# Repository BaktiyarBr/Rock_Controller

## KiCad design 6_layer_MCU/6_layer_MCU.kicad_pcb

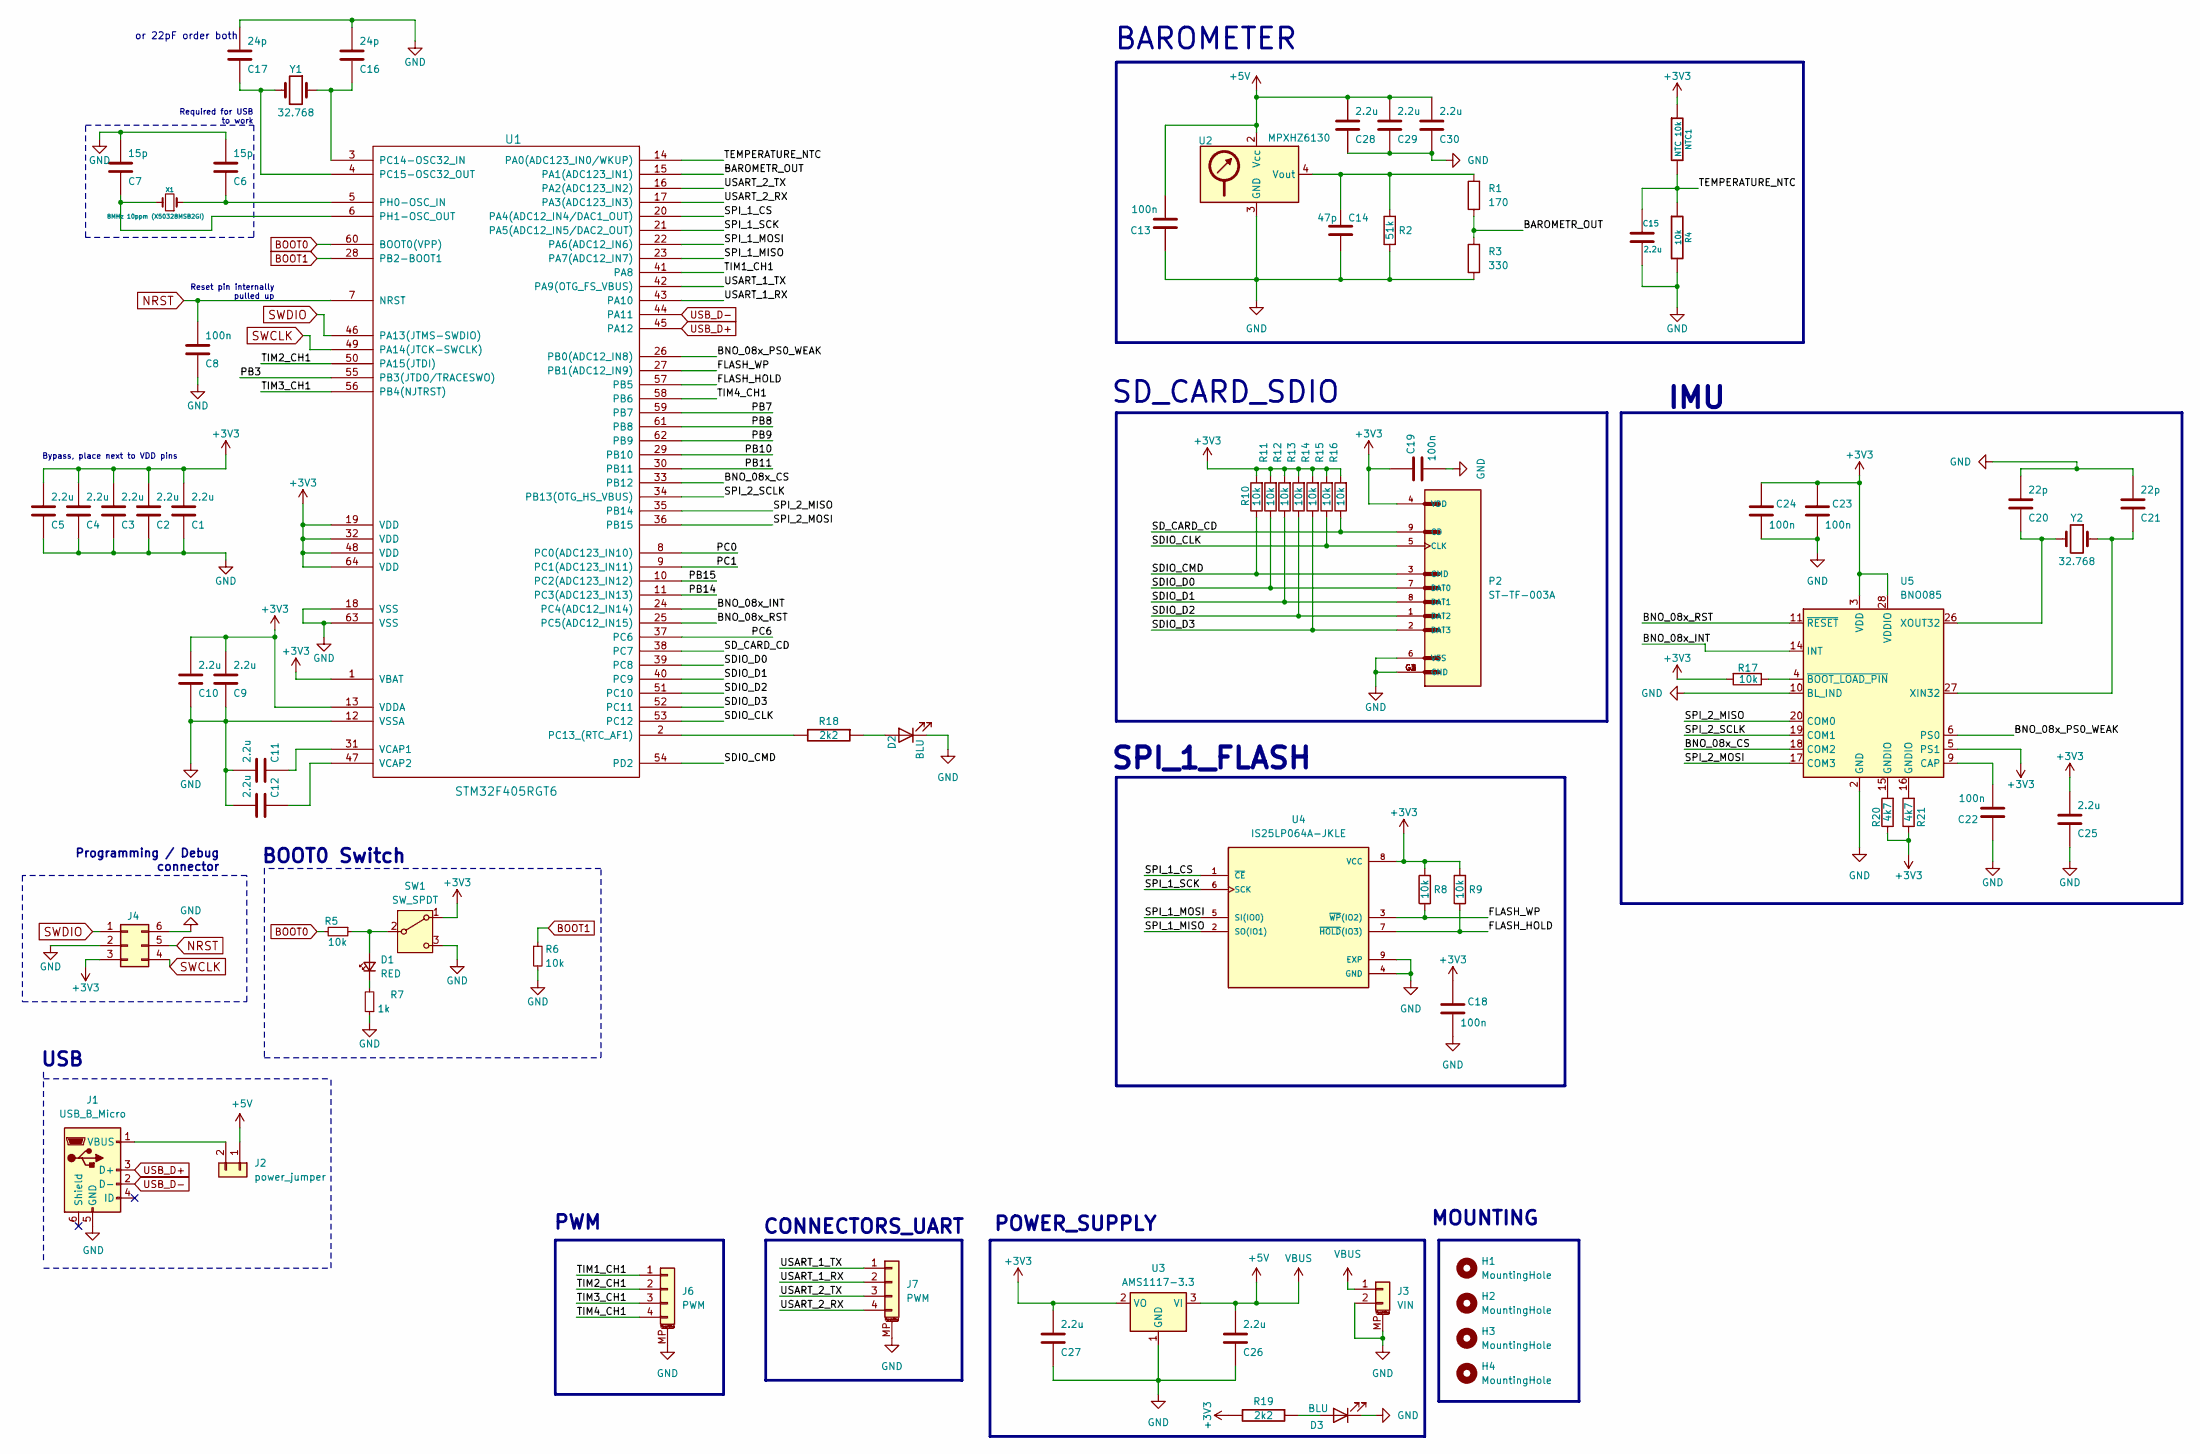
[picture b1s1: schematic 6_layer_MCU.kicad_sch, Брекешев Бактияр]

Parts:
C1, C2, C3, C4, C5, C9, C10, C11, C12, C15, C25, C26, C27, C28, C29, C30: 2.2u; C_0603_1608Metric
C6, C7: 15p; C_0603_1608Metric
C8, C13, C18, C19, C22, C23, C24: 100n; C_0603_1608Metric
C14: 47p; C_0603_1608Metric_Pad1.08x0.95mm_HandSolder
C16, C17: 24p; C_0603_1608Metric
C20, C21: 22p; C_0603_1608Metric
D1: RED; LED_0603_1608Metric; LCSC Part # C2286
D2, D3: BLU; LED_0603_1608Metric
H1, H2, H3, H4: MountingHole; MountingHole_2.2mm_M2
J1: USB_B_Micro; USB_Mini-B_Lumberg_2486_01_Horizontal
J2: power_jumper; PinHeader_1x02_P1.00mm_Vertical
J3: VIN; JST_GH_SM02B-GHS-TB_1x02-1MP_P1.25mm_Horizontal
J4: Conn_02x03_Counter_Clockwise; PinHeader_2x03_P2.54mm_Vertical
J6, J7: PWM; JST_GH_SM04B-GHS-TB_1x04-1MP_P1.25mm_Horizontal
NTC1: NTC 10k; R_0603_1608Metric
P2: ST-TF-003A; SUNTECH_ST-TF-003A
R1: 170; R_0402_1005Metric_Pad0.72x0.64mm_HandSolder
R2: 51k; R_0402_1005Metric_Pad0.72x0.64mm_HandSolder
R3: 330; R_0402_1005Metric_Pad0.72x0.64mm_HandSolder
R4, R8, R9, R10, R11, R12, R13, R14, R15, R16, R17: 10k; R_0402_1005Metric_Pad0.72x0.64mm_HandSolder
R5, R6: 10k; R_0402_1005Metric_Pad0.72x0.64mm_HandSolder; LCSC Part # C25744
R7: 1k; R_0402_1005Metric_Pad0.72x0.64mm_HandSolder; LCSC Part # C21190
R18, R19: 2k2; R_0402_1005Metric_Pad0.72x0.64mm_HandSolder
R20, R21: 4k7; R_0402_1005Metric_Pad0.72x0.64mm_HandSolder
SW1: SW_SPDT; SW_SPDT_PCM12
U1: STM32F405RGT6; LQFP-64_10x10mm_P0.5mm
U2: MPXHZ6130; SOIC-8_7.5x5.85mm_P1.27mm
U3: AMS1117-3.3; SOT-223-3_TabPin2
U4: IS25LP064A-JKLE; SON127P500X600X80-9N
U5: BNO085; LGA-28_5.2x3.8mm_P0.5mm
X1: 8MHz 10ppm (X50328MSB2GI); Crystal_SMD_5032-2Pin_5.0x3.2mm; mfg# ABM3B-8.0-10-1UT
Y1, Y2: 32.768; Crystal_SMD_3215-2Pin_3.2x1.5mm

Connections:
+3V3: C1.2, C2.2, C3.2, C4.2, C5.2, C9.2, C10.2, C18.1, C19.1, C23.1, C24.1, C25.2, C27.2, J4.3, NTC1.1, P2.4 (VDD), R8.2, R9.2, R10.2, R11.2, R12.2, R13.2, R14.2, R15.2, R16.2, R17.2, R19.2, R20.1, R21.1, SW1.1 (A), U1.1 (VBAT), U1.13 (VDDA), U1.19 (VDD), U1.32 (VDD), U1.48 (VDD), U1.64 (VDD), U3.2 (VO), U4.8 (VCC), U5.3 (VDD), U5.5 (PS1), U5.28 (VDDIO)
+5V: C13.2, C26.2, C28.2, C29.2, C30.2, J2.1, J3.1, U2.2 (Vcc), U3.3 (VI)
/BAROMETR_OUT: R1.1, R3.2, U1.15 (PA1(ADC123_IN1))
/BNO_08x_CS: U1.33 (PB12), U5.18 (COM2)
/BNO_08x_INT: U1.24 (PC4(ADC12_IN14)), U5.14 (INT)
/BNO_08x_PS0_WEAK: U1.26 (PB0(ADC12_IN8)), U5.6 (PS0)
/BNO_08x_RST: U1.25 (PC5(ADC12_IN15)), U5.11 (~RESET)
/FLASH_HOLD: R9.1, U1.57 (PB5), U4.7 (~HOLD(IO3))
/FLASH_WP: R8.1, U1.27 (PB1(ADC12_IN9)), U4.3 (~WP(IO2))
/PB3: U1.55 (PB3(JTDO/TRACESWO))
/PB7: U1.59 (PB7)
/PB8: U1.61 (PB8)
/PB9: U1.62 (PB9)
/PB10: U1.29 (PB10)
/PB11: U1.30 (PB11)
/PB14: U1.11 (PC3(ADC123_IN13))
/PB15: U1.10 (PC2(ADC123_IN12))
/PC0: U1.8 (PC0(ADC123_IN10))
/PC1: U1.9 (PC1(ADC123_IN11))
/PC6: U1.37 (PC6)
/SDIO_CLK: P2.5 (CLK), R15.1, U1.53 (PC12)
/SDIO_CMD: P2.3 (CMD), R10.1, U1.54 (PD2)
/SDIO_D0: P2.7 (DAT0), R11.1, U1.39 (PC8)
/SDIO_D1: P2.8 (DAT1), R12.1, U1.40 (PC9)
/SDIO_D2: P2.1 (DAT2), R13.1, U1.51 (PC10)
/SDIO_D3: P2.2 (DAT3), R14.1, U1.52 (PC11)
/SD_CARD_CD: P2.9 (CD), R16.1, U1.38 (PC7)
/SPI_1_CS: U1.20 (PA4(ADC12_IN4/DAC1_OUT)), U4.1 (~CE)
/SPI_1_MISO: U1.23 (PA7(ADC12_IN7)), U4.2 (SO(IO1))
/SPI_1_MOSI: U1.22 (PA6(ADC12_IN6)), U4.5 (SI(IO0))
/SPI_1_SCK: U1.21 (PA5(ADC12_IN5/DAC2_OUT)), U4.6 (SCK)
/SPI_2_MISO: U1.35 (PB14), U5.20 (COM0)
/SPI_2_MOSI: U1.36 (PB15), U5.17 (COM3)
/SPI_2_SCLK: U1.34 (PB13(OTG_HS_VBUS)), U5.19 (COM1)
/TEMPERATURE_NTC: C15.1, NTC1.2, R4.1, U1.14 (PA0(ADC123_IN0/WKUP))
/TIM1_CH1: J6.1, U1.41 (PA8)
/TIM2_CH1: J6.2, U1.50 (PA15(JTDI))
/TIM3_CH1: J6.3, U1.56 (PB4(NJTRST))
/TIM4_CH1: J6.4, U1.58 (PB6)
/USART_1_RX: J7.2, U1.43 (PA10)
/USART_1_TX: J7.1, U1.42 (PA9(OTG_FS_VBUS))
/USART_2_RX: J7.4, U1.17 (PA3(ADC123_IN3))
/USART_2_TX: J7.3, U1.16 (PA2(ADC123_IN2))
BOOT0: R5.2, U1.60 (BOOT0(VPP))
BOOT1: R6.1, U1.28 (PB2-BOOT1)
GND: C1.1, C2.1, C3.1, C4.1, C5.1, C6.2, C7.2, C8.1, C9.1, C10.1, C11.2, C12.2, C13.1, C14.2, C15.2, C16.2, C17.2, C18.2, C19.2, C20.2, C21.2, C22.1, C23.2, C24.2, C25.1, C26.1, C27.1, C28.1, C29.1, C30.1, D2.1 (K), D3.1 (K), J1.5 (GND), J3.2, J3.MP (MountPin), J4.2, J4.6, J6.MP (MountPin), J7.MP (MountPin), P2.6 (VSS), P2.G1 (GND), P2.G2 (GND), P2.G3 (GND), P2.G4 (GND), R2.1, R3.1, R4.2, R6.2, R7.1, SW1.3 (C), U1.12 (VSSA), U1.18 (VSS), U1.63 (VSS), U2.3 (GND), U3.1 (GND), U4.4 (GND), U4.9 (EXP), U5.2 (GND), U5.10 (BL_IND)
NRST: C8.2, J4.5, U1.7 (NRST)
unnamed: D1.2 (A), R5.1, SW1.2 (B)
unnamed: D1.1 (K), R7.2
unnamed: D2.2 (A), R18.1
unnamed: D3.2 (A), R19.1
unnamed: J1.1 (VBUS), J2.2
unnamed: R20.2, U5.15 (GNDIO)
unnamed: R21.2, U5.16 (GNDIO)
unnamed: R18.2, U1.2 (PC13_(RTC_AF1))
unnamed: C16.1, U1.3 (PC14-OSC32_IN), Y1.1
unnamed: C17.1, U1.4 (PC15-OSC32_OUT), Y1.2
unnamed: C6.1, U1.5 (PH0-OSC_IN), X1.1
unnamed: C7.1, U1.6 (PH1-OSC_OUT), X1.2
unnamed: C11.1, U1.31 (VCAP1)
unnamed: C12.1, U1.47 (VCAP2)
unnamed: C14.1, R1.2, R2.2, U2.4 (Vout)
unnamed: C22.2, U5.9 (CAP)
unnamed: C21.1, U5.27 (XIN32), Y2.1
unnamed: C20.1, U5.26 (XOUT32), Y2.2
unnamed: R17.1, U5.4 (~BOOT_LOAD_PIN)
SWCLK: J4.4, U1.49 (PA14(JTCK-SWCLK))
SWDIO: J4.1, U1.46 (PA13(JTMS-SWDIO))
USB_D+: J1.3 (D+), U1.45 (PA12)
USB_D-: J1.2 (D-), U1.44 (PA11)

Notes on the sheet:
IMU
SD_CARD_SDIO
CONNECTORS_UART
Reset pin internally pulled up
BAROMETER
or 22pF order both
USB
Bypass, place next to VDD pins
PWM
Required for USB to work
MOUNTING
Programming / Debug connector
BOOT0 Switch
SPI_1_FLASH
POWER_SUPPLY

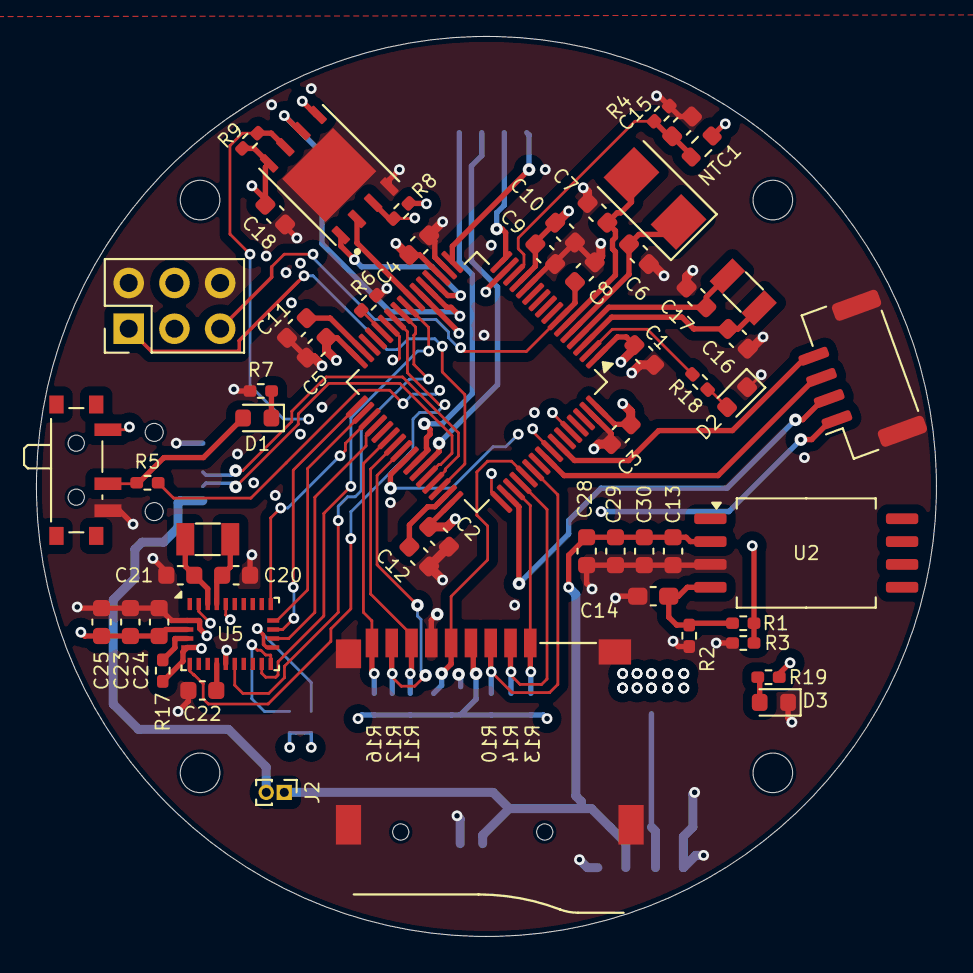
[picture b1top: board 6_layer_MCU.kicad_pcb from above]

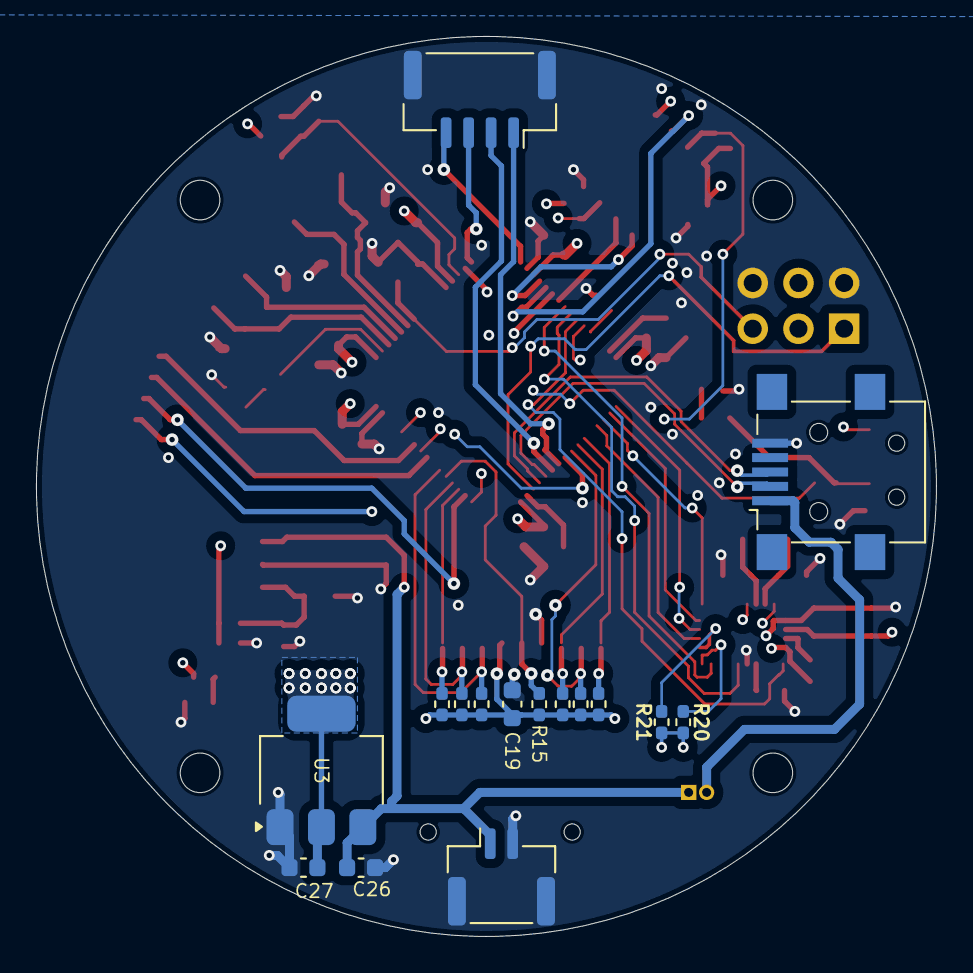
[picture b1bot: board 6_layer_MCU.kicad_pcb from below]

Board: 6 copper layers, 50.0 x 50.0 mm, 75 parts (16 on the bottom side), 59 nets.

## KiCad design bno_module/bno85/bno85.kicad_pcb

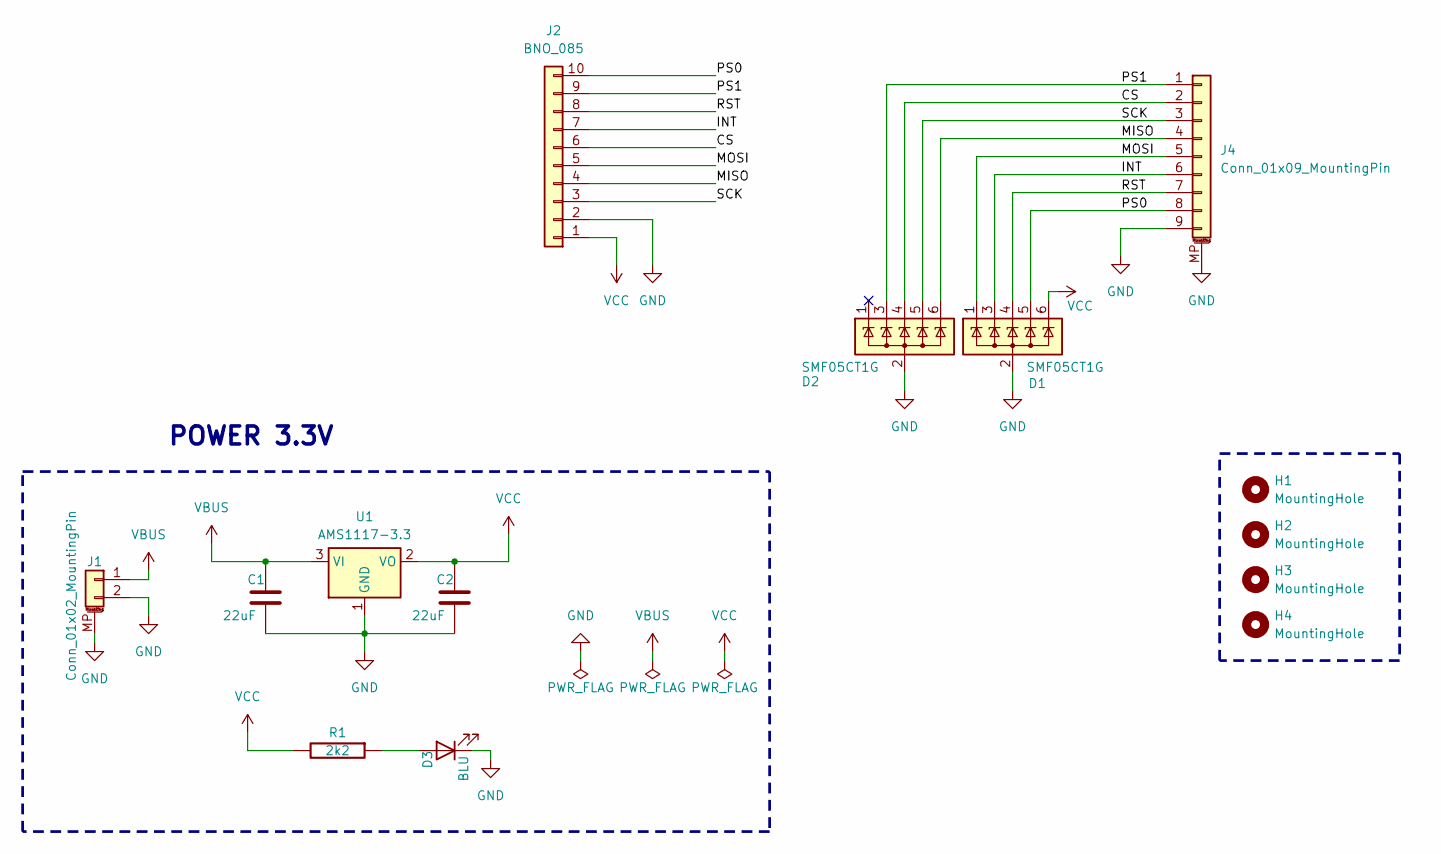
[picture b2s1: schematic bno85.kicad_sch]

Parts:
C1, C2: 22uF; C_0805_2012Metric
D1, D2: SMF05CT1G; SOT-363_SC-70-6
D3: BLU; LED_0603_1608Metric
H1, H2, H3, H4: MountingHole; MountingHole_2.2mm_M2
J1: Conn_01x02_MountingPin; JST_GH_SM02B-GHS-TB_1x02-1MP_P1.25mm_Horizontal
J2: BNO_085; PinHeader_1x10_P2.54mm_Vertical
J4: Conn_01x09_MountingPin; JST_GH_SM09B-GHS-TB_1x09-1MP_P1.25mm_Horizontal
R1: 2k2; R_0603_1608Metric
U1: AMS1117-3.3; SOT-223-3_TabPin2

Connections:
/CS: D2.4 (K), J2.6, J4.2
/INT: D1.3 (K), J2.7, J4.6
/MISO: D2.6 (K), J2.4, J4.4
/MOSI: D1.1 (K), J2.5, J4.5
/PS0: D1.5 (K), J2.10, J4.8
/PS1: D2.3 (K), J2.9, J4.1
/RST: D1.4 (K), J2.8, J4.7
/SCK: D2.5 (K), J2.3, J4.3
GND: C1.1, C2.1, D1.2 (A), D2.2 (A), D3.1 (K), J1.2, J1.MP (MountPin), J2.2, J4.9, J4.MP (MountPin), U1.1 (GND)
unnamed: D3.2 (A), R1.1
VBUS: C1.2, J1.1, U1.3 (VI)
VCC: C2.2, D1.6 (K), J2.1, R1.2, U1.2 (VO)

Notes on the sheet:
POWER 3.3V

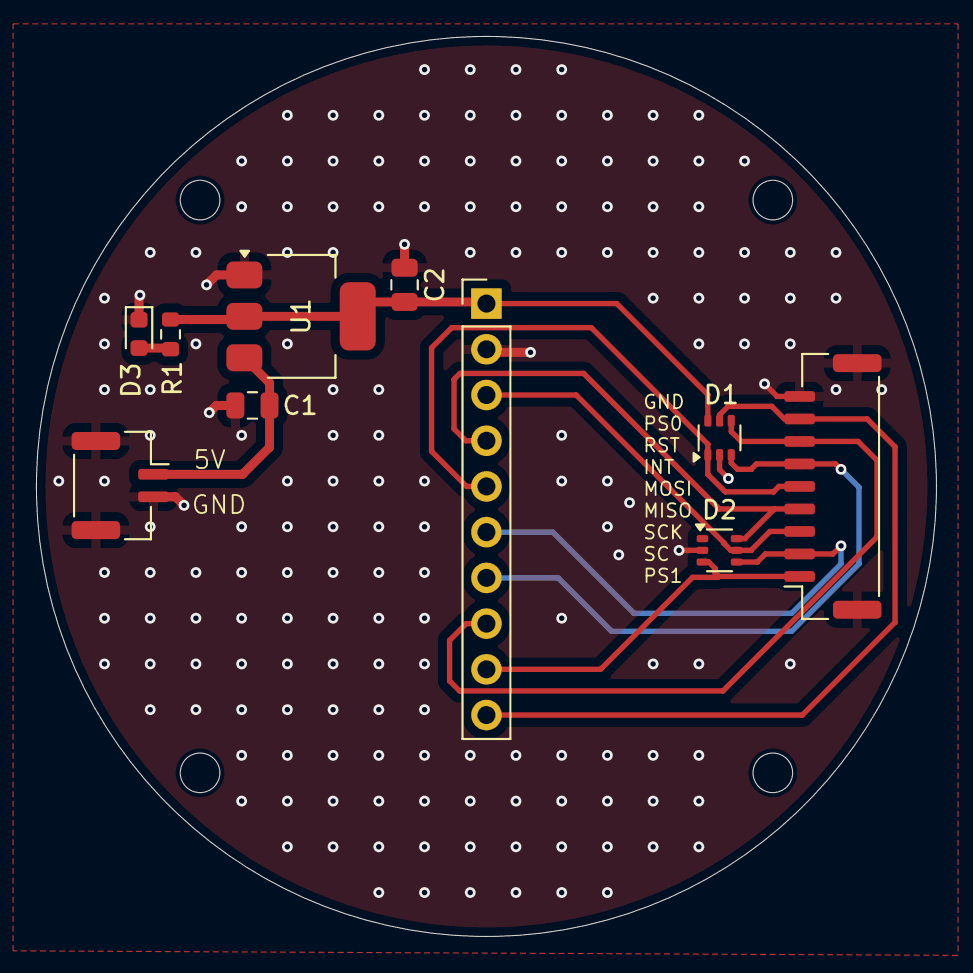
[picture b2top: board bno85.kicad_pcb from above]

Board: 4 copper layers, 50.0 x 50.0 mm, 14 parts (0 on the bottom side), 12 nets.

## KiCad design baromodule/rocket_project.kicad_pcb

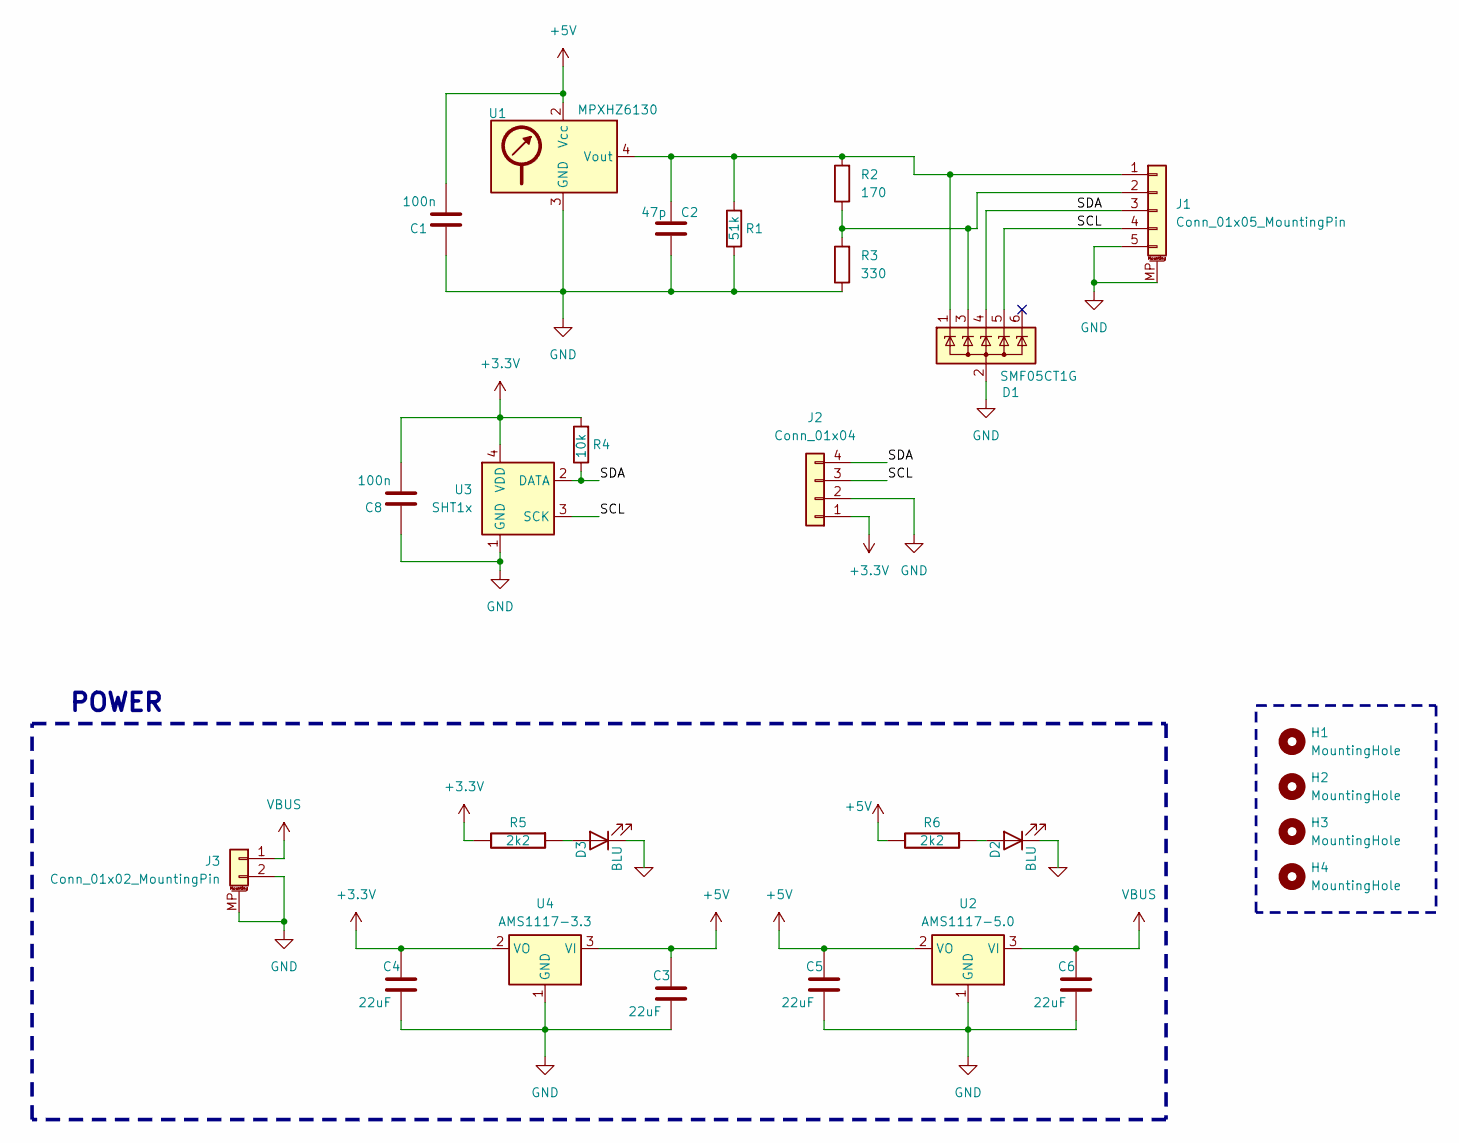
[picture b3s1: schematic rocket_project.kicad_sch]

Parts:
C1, C8: 100n; C_0603_1608Metric
C2: 47p; C_0603_1608Metric_Pad1.08x0.95mm_HandSolder
C3, C4, C5, C6: 22uF; C_0805_2012Metric
D1: SMF05CT1G; SOT-363_SC-70-6
D2, D3: BLU; LED_0603_1608Metric
H1, H2, H3, H4: MountingHole; MountingHole_2.2mm_M2
J1: Conn_01x05_MountingPin; JST_GH_SM05B-GHS-TB_1x05-1MP_P1.25mm_Horizontal
J2: Conn_01x04; PinSocket_1x04_P2.54mm_Vertical
J3: Conn_01x02_MountingPin; JST_GH_SM02B-GHS-TB_1x02-1MP_P1.25mm_Horizontal
R1: 51k; R_0603_1608Metric_Pad0.98x0.95mm_HandSolder
R2: 170; R_0603_1608Metric_Pad0.98x0.95mm_HandSolder
R3: 330; R_0603_1608Metric_Pad0.98x0.95mm_HandSolder
R4: 10k; R_0603_1608Metric_Pad0.98x0.95mm_HandSolder
R5, R6: 2k2; R_0603_1608Metric
U1: MPXHZ6130; SOIC-8_7.5x5.85mm_P1.27mm
U2: AMS1117-5.0; SOT-223-3_TabPin2
U3: SHT1x
U4: AMS1117-3.3; SOT-223-3_TabPin2

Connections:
+3.3V: C4.2, C8.2, J2.1, R4.2, R5.2, U3.4 (VDD), U4.2 (VO)
+5V: C1.2, C3.2, C5.2, R6.2, U1.2 (Vcc), U2.2 (VO), U4.3 (VI)
/SCL: D1.5 (K), J1.4, J2.3, U3.3 (SCK)
/SDA: D1.4 (K), J1.3, J2.4, R4.1, U3.2 (DATA)
GND: C1.1, C2.2, C3.1, C4.1, C5.1, C6.1, C8.1, D1.2 (A), D2.1 (K), D3.1 (K), J1.5, J1.MP (MountPin), J2.2, J3.2, J3.MP (MountPin), R1.1, R3.1, U1.3 (GND), U2.1 (GND), U3.1 (GND), U4.1 (GND)
unnamed: D2.2 (A), R6.1
unnamed: D3.2 (A), R5.1
unnamed: C2.1, D1.1 (K), J1.1, R1.2, R2.2, U1.4 (Vout)
unnamed: D1.3 (K), J1.2, R2.1, R3.2
VBUS: C6.2, J3.1, U2.3 (VI)

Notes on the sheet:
POWER

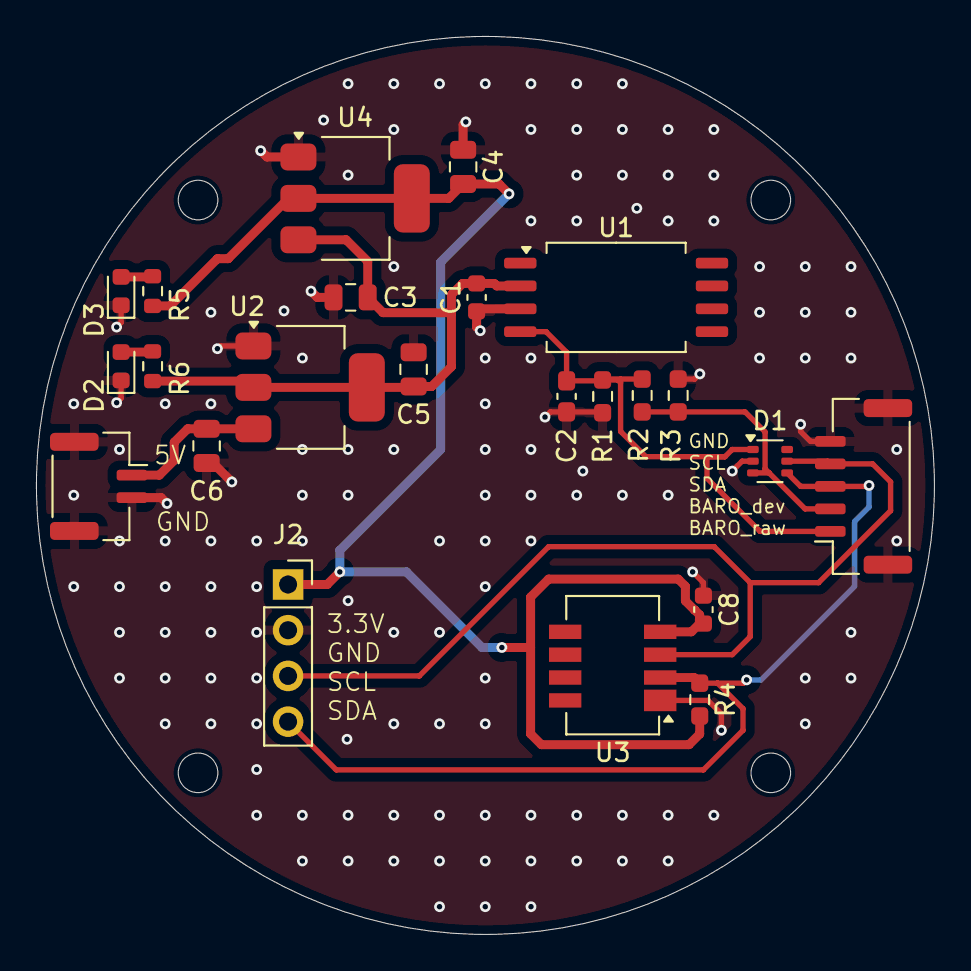
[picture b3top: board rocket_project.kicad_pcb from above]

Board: 4 copper layers, 49.9 x 49.9 mm, 27 parts (0 on the bottom side), 10 nets.

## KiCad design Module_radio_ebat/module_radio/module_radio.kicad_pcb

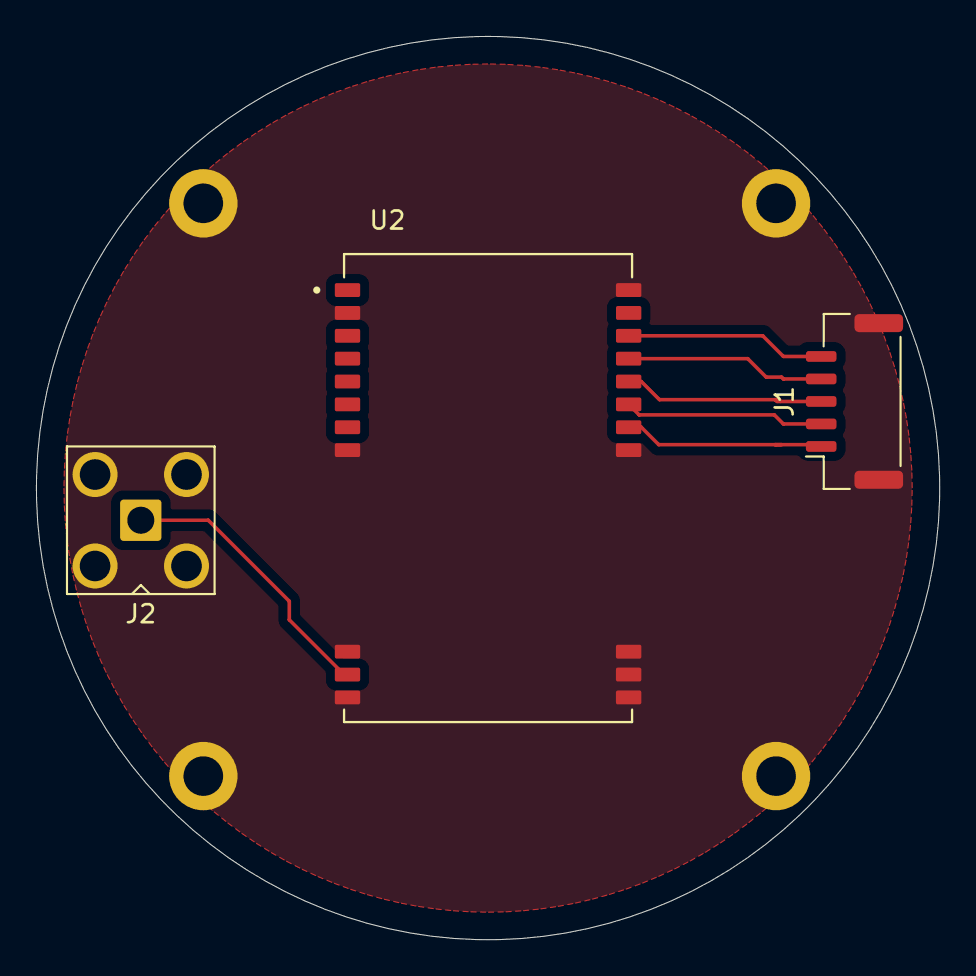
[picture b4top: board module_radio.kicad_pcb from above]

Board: 2 copper layers, 50.2 x 50.2 mm, 7 parts (0 on the bottom side), 7 nets.

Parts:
H1, H2, H3, H4: MountingHole_Pad; MountingHole_2.2mm_M2_DIN965_Pad
J1: Conn_01x05_MountingPin; JST_GH_SM05B-GHS-TB_1x05-1MP_P1.25mm_Horizontal
J2: Conn_Coaxial_Small; SMA_Amphenol_901-143_Horizontal
U2: E32-433T30S; MODULE_E32-433T20S

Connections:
/AUX: J1.5, U2.24 (AUX)
/M0: J1.1, U2.20 (M0)
/M1: J1.2, U2.21 (M1)
/RXD: J1.3, U2.22 (RXD)
/TXD: J1.4, U2.23 (TXD)
GND: H1.1, H2.1, H3.1, H4.1, J1.MP (MountPin), J2.2 (Ext), U2.2 (GND), U2.8 (GND), U2.11 (GND), U2.13 (GND), U2.14 (GND), U2.15 (GND), U2.16 (GND), U2.19 (GND), U2.26 (GND)
unnamed: J2.1 (In), U2.12 (ANT)

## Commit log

2024-05-22 6-layer
2024-07-29 final
